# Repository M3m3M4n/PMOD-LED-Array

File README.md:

# PMOD LED ARRAY

Dual PMOD 16 LEDs Array

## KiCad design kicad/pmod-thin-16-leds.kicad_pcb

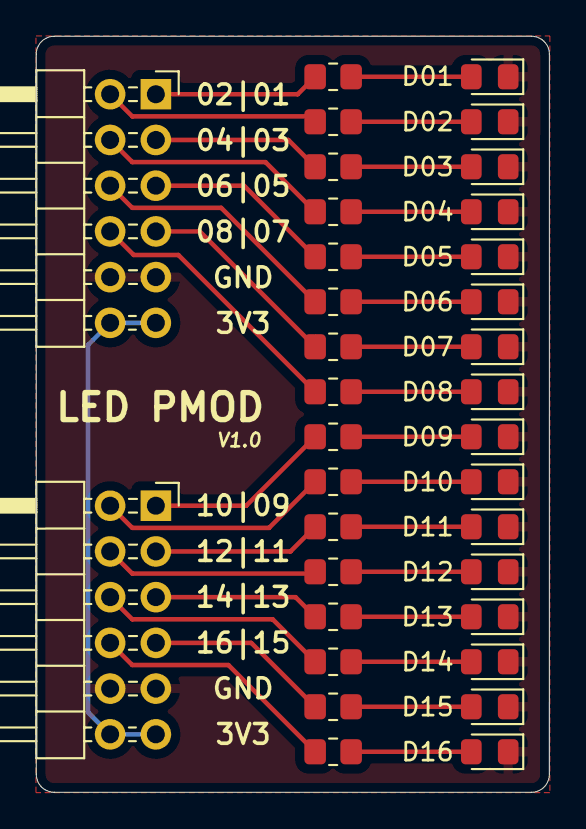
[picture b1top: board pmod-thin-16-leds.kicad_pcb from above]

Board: 2 copper layers, 28.5 x 42.0 mm, 34 parts (0 on the bottom side), 34 nets.

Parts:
D01, D02, D03, D04, D05, D06, D07, D08, D09, D10, D11, D12, D13, D14, D15, D16: LED; LED_0805_2012Metric_Pad1.15x1.40mm_HandSolder
J1, J2: PMOD; Pmod_Header_2x06_P2.54mm_Horizontal
R1, R2, R3, R4, R5, R6, R7, R8, R9, R10, R11, R12, R13, R14, R15, R16: 220; R_0805_2012Metric_Pad1.20x1.40mm_HandSolder

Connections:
+3V3: J1.6 (3.3V), J1.12 (3.3V), J2.6 (3.3V), J2.12 (3.3V)
/p1: J1.1, R1.1
/p2: J1.7, R2.1
/p3: J1.2, R3.1
/p4: J1.8, R4.1
/p5: J1.3, R5.1
/p6: J1.9, R6.1
/p7: J1.4, R7.1
/p8: J1.10, R8.1
/p9: J2.1, R9.1
/p10: J2.7, R10.1
/p11: J2.2, R11.1
/p12: J2.8, R12.1
/p13: J2.3, R13.1
/p14: J2.9, R14.1
/p15: J2.4, R15.1
/p16: J2.10, R16.1
GND: D01.1 (K), D02.1 (K), D03.1 (K), D04.1 (K), D05.1 (K), D06.1 (K), D07.1 (K), D08.1 (K), D09.1 (K), D10.1 (K), D11.1 (K), D12.1 (K), D13.1 (K), D14.1 (K), D15.1 (K), D16.1 (K), J1.5 (GND), J1.11 (GND), J2.5 (GND), J2.11 (GND)
unnamed: D01.2 (A), R1.2
unnamed: D02.2 (A), R2.2
unnamed: D03.2 (A), R3.2
unnamed: D04.2 (A), R4.2
unnamed: D05.2 (A), R5.2
unnamed: D06.2 (A), R6.2
unnamed: D07.2 (A), R7.2
unnamed: D08.2 (A), R8.2
unnamed: D09.2 (A), R9.2
unnamed: D10.2 (A), R10.2
unnamed: D11.2 (A), R11.2
unnamed: D12.2 (A), R12.2
unnamed: D13.2 (A), R13.2
unnamed: D14.2 (A), R14.2
unnamed: D15.2 (A), R15.2
unnamed: D16.2 (A), R16.2

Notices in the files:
kicad/pmod-thin-16-leds.kicad_pcb:
CC-BY-SA
